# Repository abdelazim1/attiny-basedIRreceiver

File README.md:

# attiny-basedIRreceiver
IR-based remote 2-channel relay kit

Not finished

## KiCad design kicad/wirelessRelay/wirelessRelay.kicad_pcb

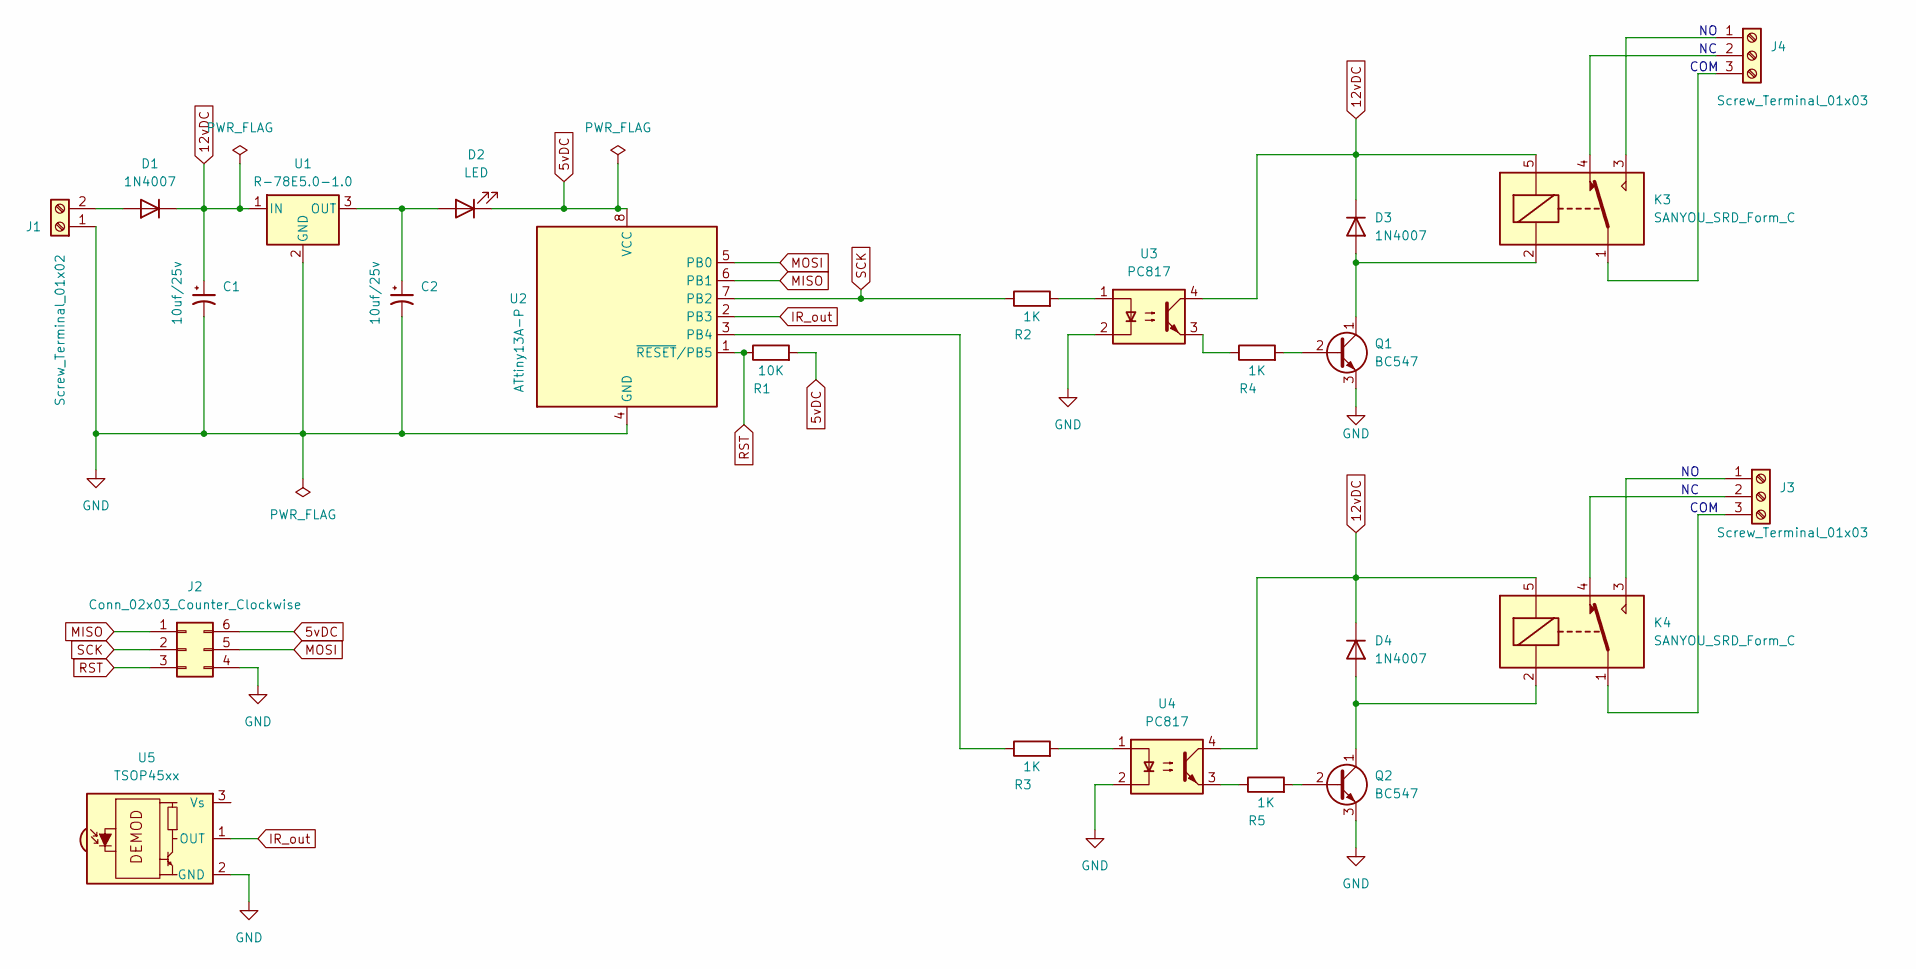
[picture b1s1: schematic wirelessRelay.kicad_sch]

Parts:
C1, C2: 10uf/25v; CP_Radial_D4.0mm_P1.50mm
D1: 1N4007; D_DO-41_SOD81_P10.16mm_Horizontal
D2: LED; LED_D4.0mm
D3, D4: 1N4007; D_DO-41_SOD81_P7.62mm_Horizontal
J1: Screw_Terminal_01x02; TerminalBlock_Phoenix_MKDS-1,5-2-5.08_1x02_P5.08mm_Horizont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
J2: Conn_02x03_Counter_Clockwise; PinHeader_2x03_P2.54mm_Vertical
J3, J4: Screw_Terminal_01x03; TerminalBlock_Phoenix_MKDS-1,5-3-5.08_1x03_P5.08mm_Horizont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
K3, K4: SANYOU_SRD_Form_C; Relay_SPDT_SANYOU_SRD_Series_Form_C
Q1, Q2: BC547; TO-92L_Inline
R1: 10K; R_Axial_DIN0204_L3.6mm_D1.6mm_P7.62mm_Horizontal
R2, R3, R4, R5: 1K; R_Axial_DIN0204_L3.6mm_D1.6mm_P7.62mm_Horizontal
U1: R-78E5.0-1.0; Converter_DCDC_RECOM_R-78E-0.5_THT
U2: ATtiny13A-P; DIP-8_W7.62mm
U3, U4: PC817; DIP-4_W7.62mm
U5: TSOP45xx; Vishay_MOLD-3Pin

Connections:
5vDC: D2.1 (K), J2.6, R1.2, U2.8 (VCC)
12vDC: C1.1, D1.1 (K), D3.1 (K), D4.1 (K), K3.5, K4.5, U1.1 (IN), U3.4, U4.4
GND: C1.2, C2.2, J1.1, J2.4, Q1.3 (E), Q2.3 (E), U1.2 (GND), U2.4 (GND), U3.2, U4.2, U5.2 (GND)
IR_out: U2.2 (PB3), U5.1 (OUT)
MISO: J2.1, U2.6 (PB1)
MOSI: J2.5, U2.5 (PB0)
unnamed: D1.2 (A), J1.2
unnamed: C2.1, D2.2 (A), U1.3 (OUT)
unnamed: D3.2 (A), K3.2, Q1.1 (C)
unnamed: D4.2 (A), K4.2, Q2.1 (C)
unnamed: J3.1, K4.3
unnamed: J3.2, K4.4
unnamed: J3.3, K4.1
unnamed: J4.1, K3.3
unnamed: J4.2, K3.4
unnamed: J4.3, K3.1
unnamed: Q1.2 (B), R4.2
unnamed: Q2.2 (B), R5.2
unnamed: R2.2, U3.1
unnamed: R3.2, U4.1
unnamed: R4.1, U3.3
unnamed: R5.1, U4.3
unnamed: R3.1, U2.3 (PB4)
RST: J2.3, R1.1, U2.1 (~RESET/PB5)
SCK: J2.2, R2.1, U2.7 (PB2)

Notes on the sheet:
COM

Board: 2 copper layers, 24 parts (0 on the bottom side), 25 nets, no tracks yet.

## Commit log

2023-07-23 v0.0_notFinished
